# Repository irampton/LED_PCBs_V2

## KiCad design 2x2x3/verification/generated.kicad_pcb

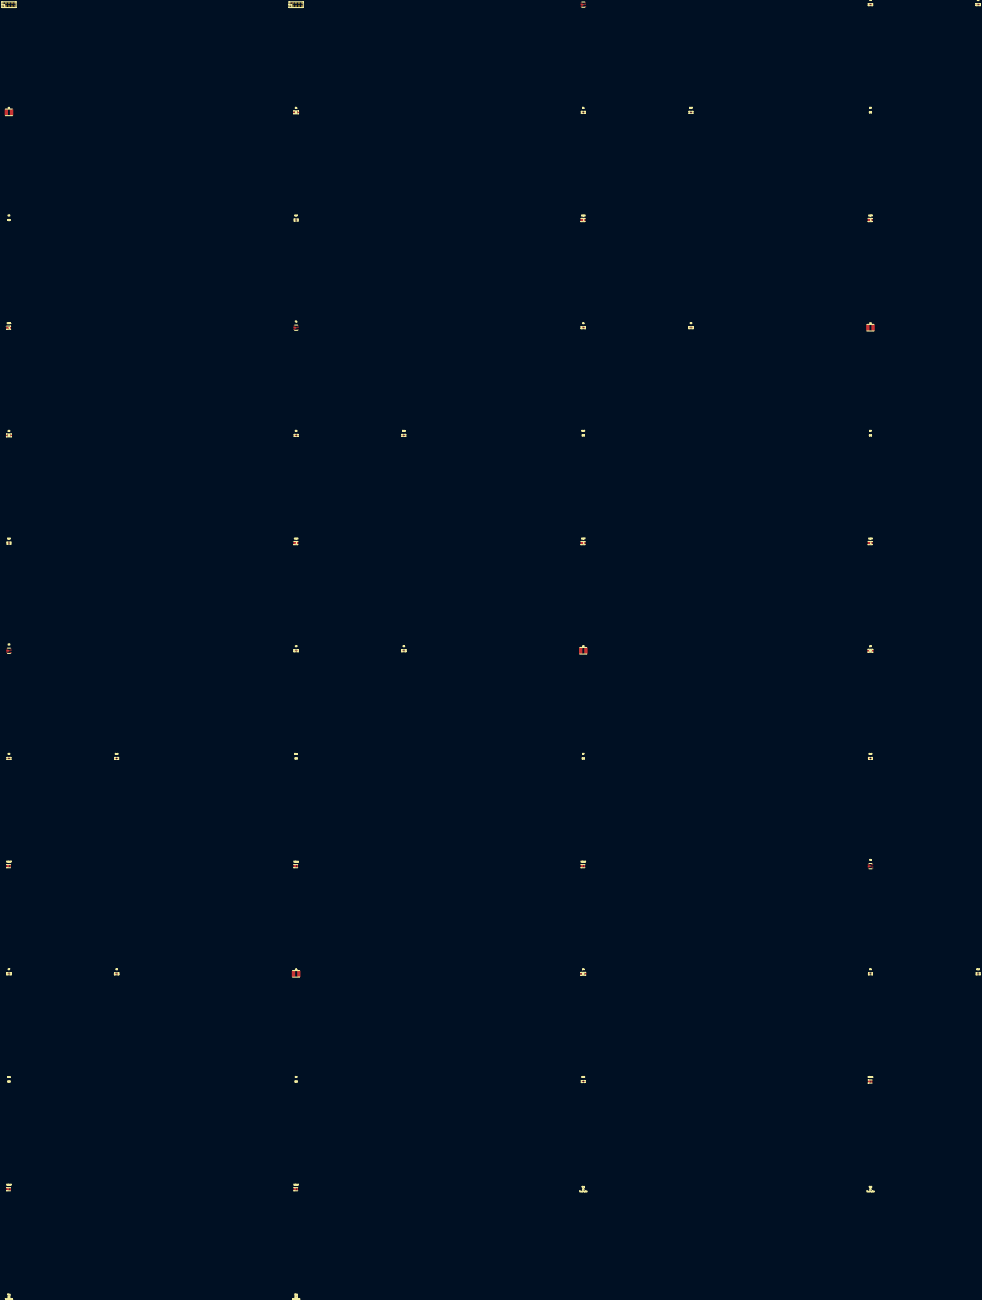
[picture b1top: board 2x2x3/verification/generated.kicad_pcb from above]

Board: 2 copper layers, 58 parts (0 on the bottom side), 28 nets, no tracks yet.

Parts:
C1, C2, C3, C4, C5, C6, C7, C8: 2.2uF; CL21A225KBQNNNE
D1, D2, D3, D4: SS14
H1, H2: PZ2.54-2X5P-H25; PZ2_54_2X5P_H25
L1, L2, L3, L4: 0.000068uH; CY54_68UH
LED2, LED3, LED4, LED6, LED7, LED8: HL-AS-2835D68W-2C-S1-08L-PCT-HR3(R9)-K3(6000K-700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; HL_AS_2835D68W_2C_S1_08L_PCT_HR3_R9_K3_6000K_7000K
LED10, LED11, LED12, LED14, LED15, LED16: HL-AS-2835D68W-2C-S1-08L-PCT-HR3(R9)-K3(2800K-310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; HL_AS_2835D68W_2C_S1_08L_PCT_HR3_R9_K3_2800K_3100K
R1, R2, R3, R4, R13, R14, R15, R16: 1.2; P_0805W8F120KT5E
R5, R6, R7, R8: 100k; P_0402WGF1003TCE
R9, R10, R11, R12: 2.2k; P_0402WGF2201TCE
R17, R18, R19, R20: 10k; P_0805W8F1002T5E
TP1: TestPoint; TestPoint_Pad_1.0x1.0mm
TP2: TestPoint; TestPoint_Pad_1.5x1.5mm
TP3, TP4: TestPoint; TestPoint_Pad_D1.0mm
U1, U2, U3, U4: PT4115

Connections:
GND: C1.2, C2.2, C3.2, C4.2, C5.2, C6.2, C7.2, C8.2, D1.2, D2.2, D3.2, D4.2, H1.2, H1.4, H1.8, H1.10, H2.2, H2.4, H2.8, H2.10, R5.2, R6.2, R7.2, R8.2, TP2.1, U1.2, U2.2, U3.2, U4.2
V+: C1.1, C2.1, C3.1, C4.1, C5.1, C6.1, C7.1, C8.1, H1.1, H1.3, H1.7, H1.9, H2.1, H2.3, H2.7, H2.9, R1.1, R2.1, R3.1, R4.1, R13.1, R14.1, R15.1, R16.1, R17.1, R18.1, R19.1, R20.1, TP1.1, U1.5, U2.5, U3.5, U4.5
cool_a_channel_LED_RETURN: L1.2, LED4.1, R17.2
cool_a_channel_LED_TOP: LED2.2, R1.2, R13.2, U2.4
cool_a_channel_driver_SW: D1.1, L1.1, U2.1
cool_a_channel_pwm_2_2_1: R5.1, R9.2, U2.3
cool_a_leds_1_2: LED2.1, LED3.2
cool_a_leds_2_2: LED3.1, LED4.2
cool_b_channel_LED_RETURN: L2.2, LED8.1, R18.2
cool_b_channel_LED_TOP: LED6.2, R2.2, R14.2, U1.4
cool_b_channel_driver_SW: D2.1, L2.1, U1.1
cool_b_channel_pwm_2_2_1: R6.1, R10.2, U1.3
cool_b_leds_1_2: LED6.1, LED7.2
cool_b_leds_2_2: LED7.1, LED8.2
pwm_cool: H1.5, H2.5, R9.1, R10.1, TP3.1
pwm_warm: H1.6, H2.6, R11.1, R12.1, TP4.1
warm_a_channel_LED_RETURN: L3.2, LED12.1, R19.2
warm_a_channel_LED_TOP: LED10.2, R3.2, R15.2, U3.4
warm_a_channel_driver_SW: D3.1, L3.1, U3.1
warm_a_channel_pwm_2_2_1: R7.1, R11.2, U3.3
warm_a_leds_1_2: LED10.1, LED11.2
warm_a_leds_2_2: LED11.1, LED12.2
warm_b_channel_LED_RETURN: L4.2, LED16.1, R20.2
warm_b_channel_LED_TOP: LED14.2, R4.2, R16.2, U4.4
warm_b_channel_driver_SW: D4.1, L4.1, U4.1
warm_b_channel_pwm_2_2_1: R8.1, R12.2, U4.3
warm_b_leds_1_2: LED14.1, LED15.2
warm_b_leds_2_2: LED15.1, LED16.2

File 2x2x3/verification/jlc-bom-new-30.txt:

JLC BOM estimate for 30 boards

Basic
Designators                 Comment             Footprint         MPN              LCSC #   JLC Stock  Per Board
--------------------------  ------------------  ----------------  ---------------  -------  ---------  ---------
C1, C2, C3, C4, C5, C6,...  2.2uF ±10% 50V X5R  0805              CL21A225KBQNNNE  C377773     965097    $0.2360
D1, D2, D3, D4                                  SMA_L4.2-W2.6...  SS14             C2480      1627295    $0.0768
R5, R6, R7, R8              100kΩ ±1% 62.5mW    0402              0402WGF1003TCE   C25741     8605915    $0.0048
R9, R10, R11, R12           2.2kΩ ±1% 62.5mW    0402              0402WGF2201TCE   C25879     3324376    $0.0044
R17, R18, R19, R20          10kΩ ±1% 125mW      0805              0805W8F1002T5E   C17414    49441463    $0.0136

Extended
Designators                 Comment          Footprint         MPN                         LCSC #     JLC Stock  Per Board
--------------------------  ---------------  ----------------  --------------------------  ---------  ---------  ---------
L1, L2, L3, L4              68uH ±10% 600mA  SMD,5.8x5.2mm     CY54-68UH                   C2929435       12384    $0.1800
LED2, LED3, LED4, LED6,...                   LED-SMD_L3.5-...  HL-AS-2835D68W-2C-S1-08...  C49435731      12953    $0.1800
LED10, LED11, LED12, LE...                   LED-SMD_L3.3-...  HL-AS-2835D68W-2C-S1-08...  C49435727       1153    $0.1830
R1, R2, R3, R4, R13, R1...  1.2Ω ±1% 125mW   0805              0805W8F120KT5E              C17381         26335    $0.0400
U1, U2, U3, U4                               SOT-89-5_L4.5...  PT4115                      C347356        96127    $0.3496

Cost estimate only. These figures ignore board size, layer count, and SMD vs manual assembly.

Economic estimate for 30 boards
  Setup: $8.00
  Stencil: $1.50
  Joints: $2.30
  Extended parts fees: $15.00
  Components: $38.05
  Total estimate: $64.85

Standard estimate for 30 boards
  Setup: $25.00
  Stencil: $7.68
  Joints @ $0.0016: $2.30
  Feed loaders: $15.00
  Components: $38.05
  Total estimate: $88.03

Economic totals
2 boards   $27.59
5 boards   $32.23
15 boards  $45.32
30 boards  $64.85

Standard totals
5 boards     $55.41
30 boards    $88.03
100 boards   $159.62
1000 boards  $960.68

Additional fees may apply: $3.50 hand-soldering, $59.23 large-sized boards, plus x-ray inspection and panel fees.
Double-sided boards require standard assembly, can add $25 setup, and add $7.86 stencil cost.

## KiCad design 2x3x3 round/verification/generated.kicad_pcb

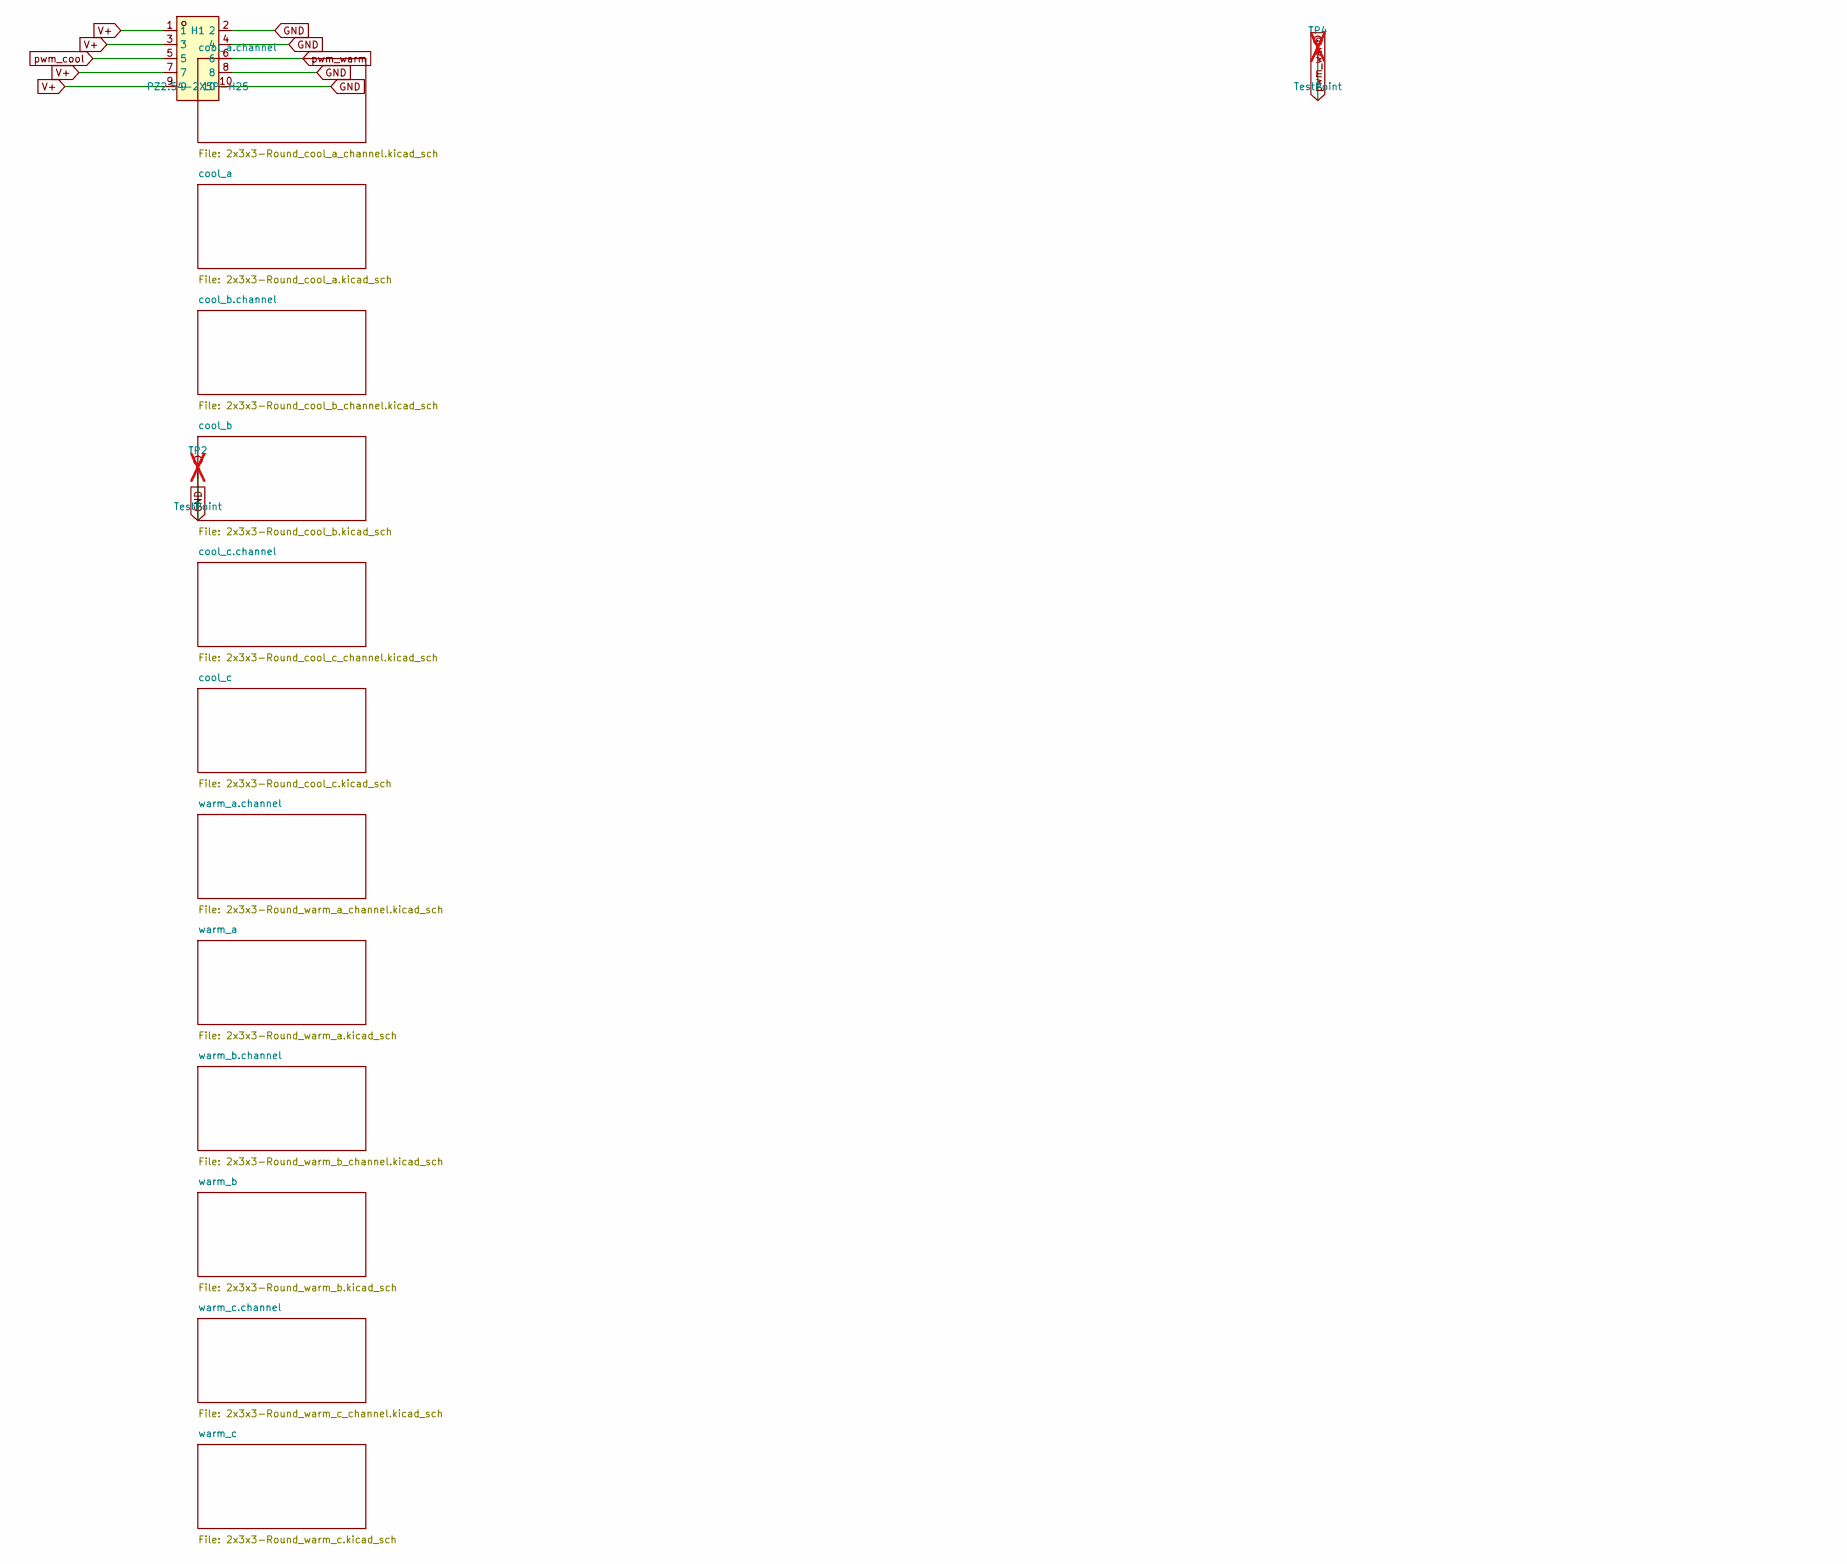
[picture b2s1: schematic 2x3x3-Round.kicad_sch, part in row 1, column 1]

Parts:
H1: PZ2.54-2X5P-H25; PZ2_54_2X5P_H25
TP1: TestPoint; TestPoint_Pad_1.0x1.0mm; not fitted
TP2: TestPoint; TestPoint_Pad_1.5x1.5mm; not fitted
TP3, TP4: TestPoint; TestPoint_Pad_D1.0mm; not fitted

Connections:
GND: H1.2, H1.4, H1.8, H1.10, TP2.1; also elsewhere on the board
V+: H1.1, H1.3, H1.7, H1.9, TP1.1; also elsewhere on the board
pwm_cool: H1.5, TP3.1; also elsewhere on the board
pwm_warm: H1.6, TP4.1; also elsewhere on the board

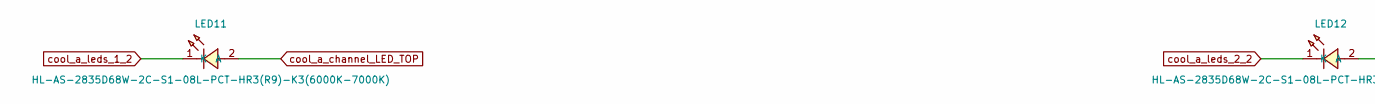
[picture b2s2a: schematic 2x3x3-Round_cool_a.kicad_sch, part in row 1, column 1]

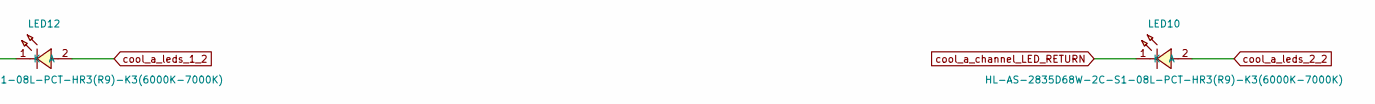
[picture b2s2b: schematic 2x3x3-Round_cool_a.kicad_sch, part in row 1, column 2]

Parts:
LED10, LED11, LED12: HL-AS-2835D68W-2C-S1-08L-PCT-HR3(R9)-K3(6000K-700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; HL_AS_2835D68W_2C_S1_08L_PCT_HR3_R9_K3_6000K_7000K

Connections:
cool_a_channel_LED_RETURN: LED10.1 (K); also elsewhere on the board
cool_a_channel_LED_TOP: LED11.2 (A); also elsewhere on the board
cool_a_leds_1_2: LED11.1 (K), LED12.2 (A)
cool_a_leds_2_2: LED10.2 (A), LED12.1 (K)

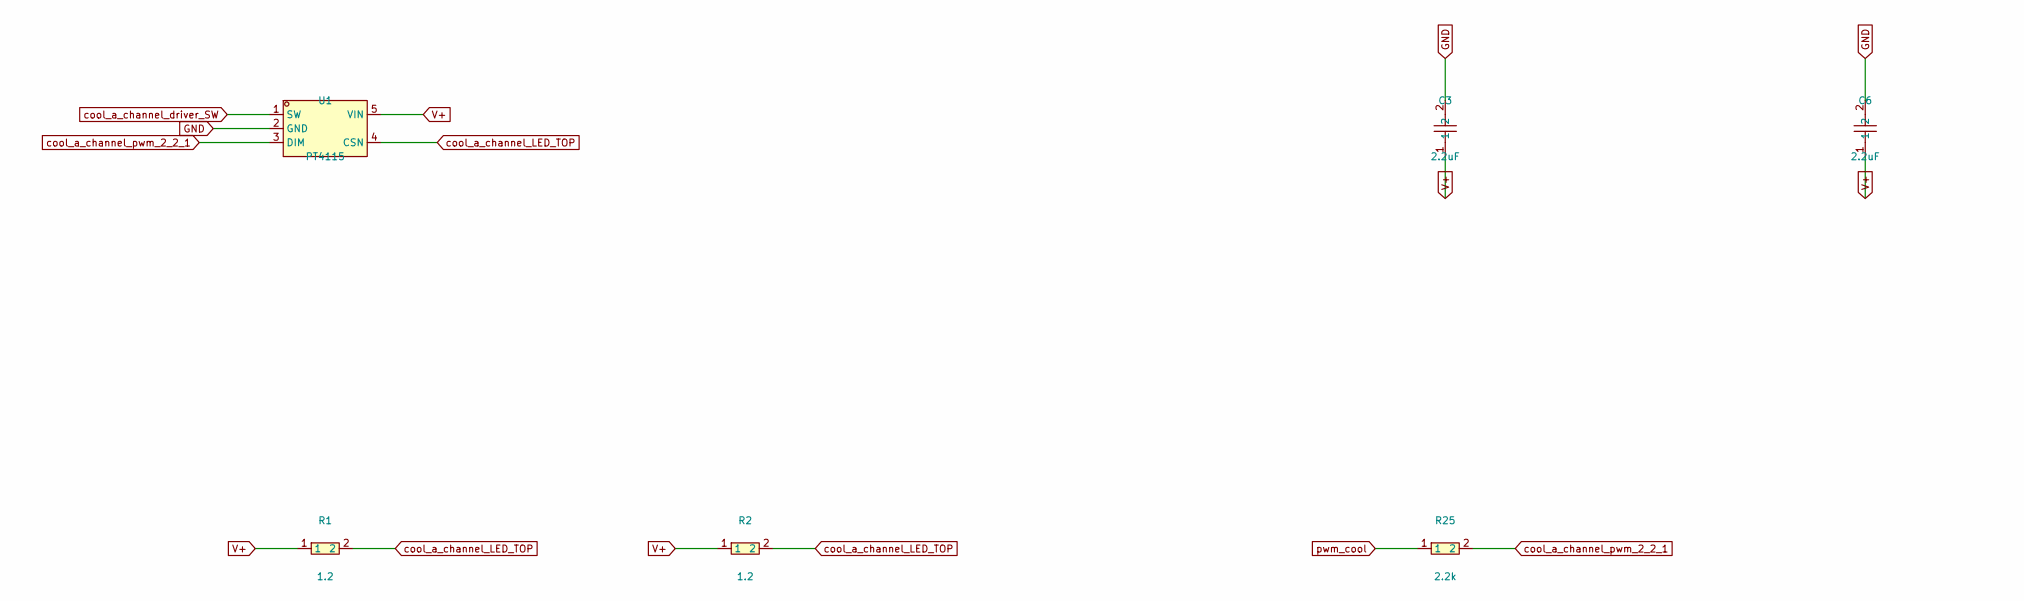
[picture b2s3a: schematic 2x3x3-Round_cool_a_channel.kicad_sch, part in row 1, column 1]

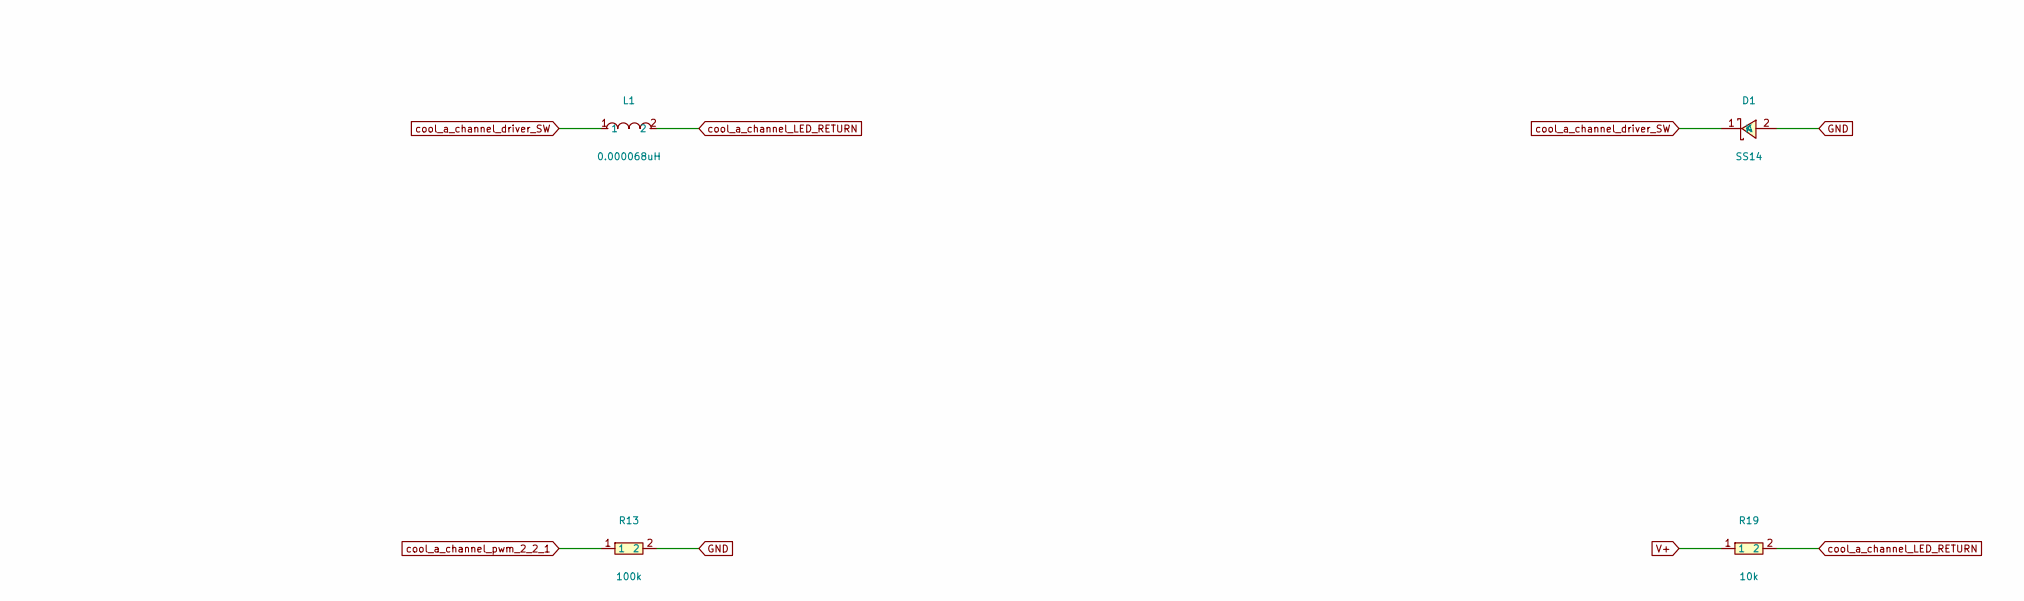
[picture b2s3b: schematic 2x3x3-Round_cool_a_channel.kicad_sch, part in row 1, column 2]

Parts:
C3, C6: 2.2uF; CL21A225KBQNNNE
D1: SS14
L1: 0.000068uH; CY54_68UH
R1, R2: 1.2; P_0805W8F120KT5E
R13: 100k; P_0402WGF1003TCE
R19: 10k; P_0805W8F1002T5E
R25: 2.2k; P_0402WGF2201TCE
U1: PT4115

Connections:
GND: C3.2, C6.2, D1.2 (A), R13.2, U1.2 (GND); also elsewhere on the board
V+: C3.1, C6.1, R1.1, R2.1, R19.1, U1.5 (VIN); also elsewhere on the board
cool_a_channel_LED_RETURN: L1.2, R19.2; also elsewhere on the board
cool_a_channel_LED_TOP: R1.2, R2.2, U1.4 (CSN); also elsewhere on the board
cool_a_channel_driver_SW: D1.1 (K), L1.1, U1.1 (SW)
cool_a_channel_pwm_2_2_1: R13.1, R25.2, U1.3 (DIM)
pwm_cool: R25.1; also elsewhere on the board

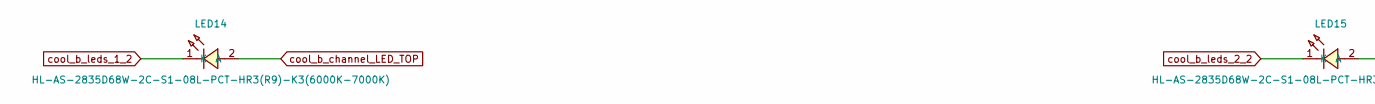
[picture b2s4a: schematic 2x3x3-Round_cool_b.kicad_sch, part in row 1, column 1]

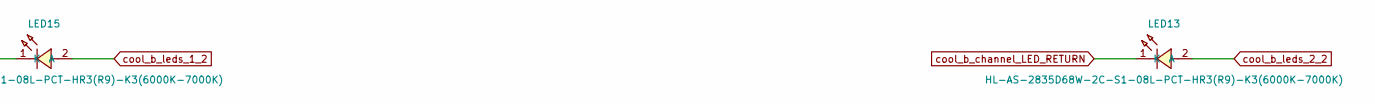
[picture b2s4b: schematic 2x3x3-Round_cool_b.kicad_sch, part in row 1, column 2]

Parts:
LED13, LED14, LED15: HL-AS-2835D68W-2C-S1-08L-PCT-HR3(R9)-K3(6000K-700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; HL_AS_2835D68W_2C_S1_08L_PCT_HR3_R9_K3_6000K_7000K

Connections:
cool_b_channel_LED_RETURN: LED13.1 (K); also elsewhere on the board
cool_b_channel_LED_TOP: LED14.2 (A); also elsewhere on the board
cool_b_leds_1_2: LED14.1 (K), LED15.2 (A)
cool_b_leds_2_2: LED13.2 (A), LED15.1 (K)

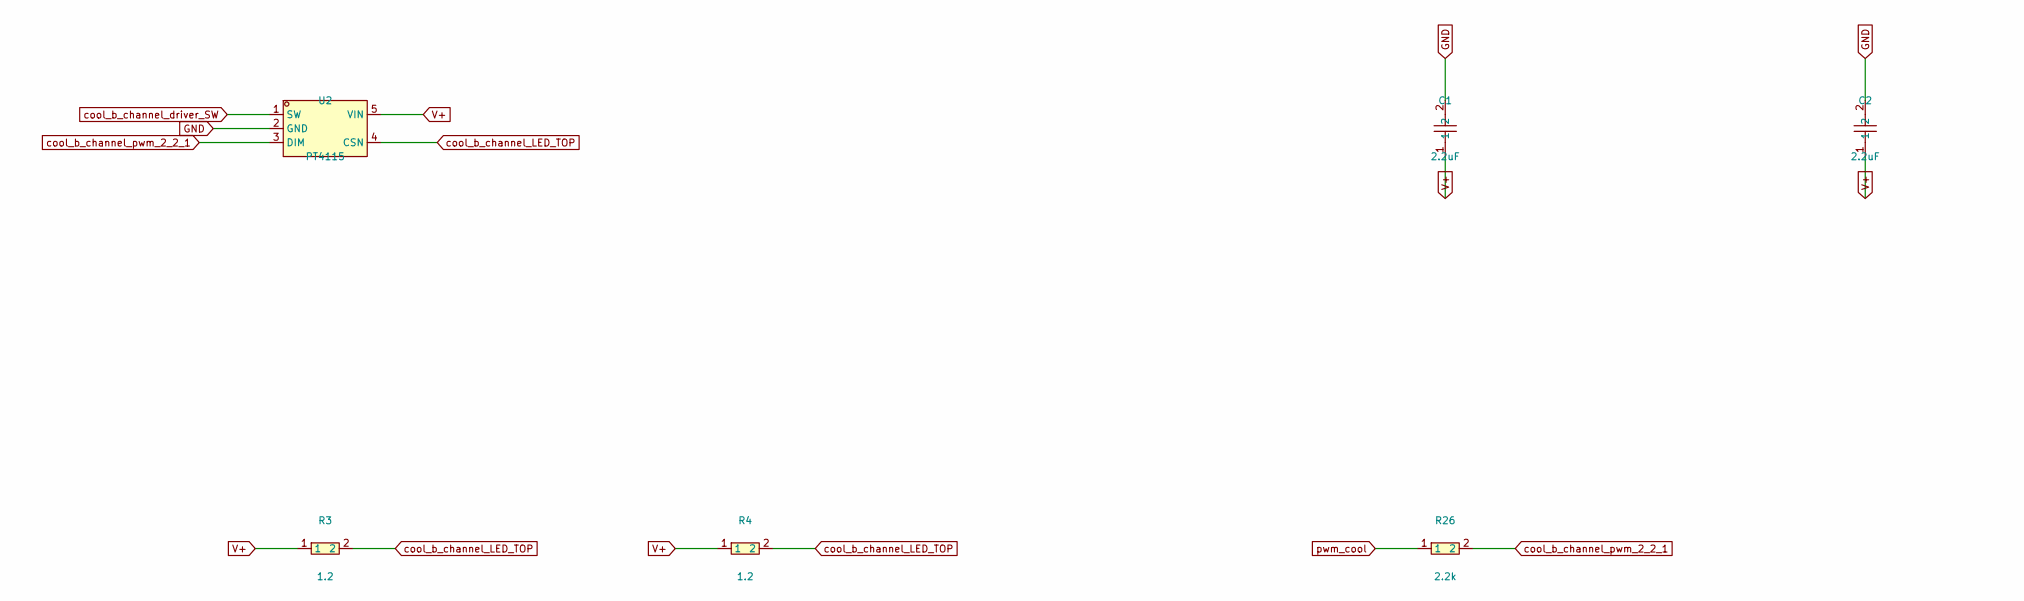
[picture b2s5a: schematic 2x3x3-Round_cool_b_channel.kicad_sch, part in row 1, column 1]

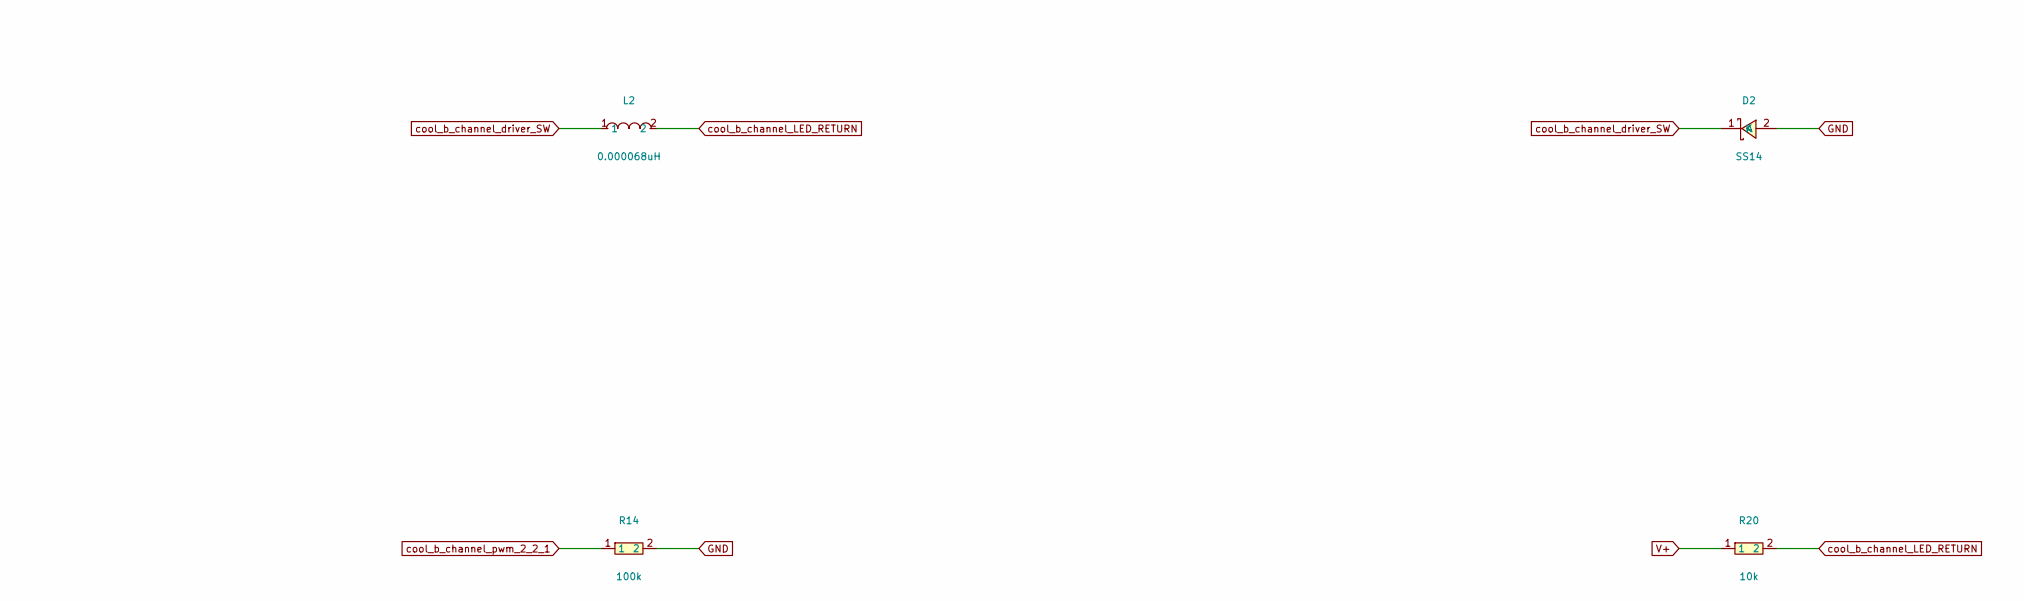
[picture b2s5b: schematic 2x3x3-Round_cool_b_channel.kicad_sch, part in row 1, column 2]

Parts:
C1, C2: 2.2uF; CL21A225KBQNNNE
D2: SS14
L2: 0.000068uH; CY54_68UH
R3, R4: 1.2; P_0805W8F120KT5E
R14: 100k; P_0402WGF1003TCE
R20: 10k; P_0805W8F1002T5E
R26: 2.2k; P_0402WGF2201TCE
U2: PT4115

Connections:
GND: C1.2, C2.2, D2.2 (A), R14.2, U2.2 (GND); also elsewhere on the board
V+: C1.1, C2.1, R3.1, R4.1, R20.1, U2.5 (VIN); also elsewhere on the board
cool_b_channel_LED_RETURN: L2.2, R20.2; also elsewhere on the board
cool_b_channel_LED_TOP: R3.2, R4.2, U2.4 (CSN); also elsewhere on the board
cool_b_channel_driver_SW: D2.1 (K), L2.1, U2.1 (SW)
cool_b_channel_pwm_2_2_1: R14.1, R26.2, U2.3 (DIM)
pwm_cool: R26.1; also elsewhere on the board

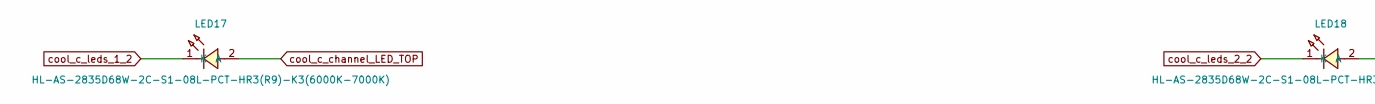
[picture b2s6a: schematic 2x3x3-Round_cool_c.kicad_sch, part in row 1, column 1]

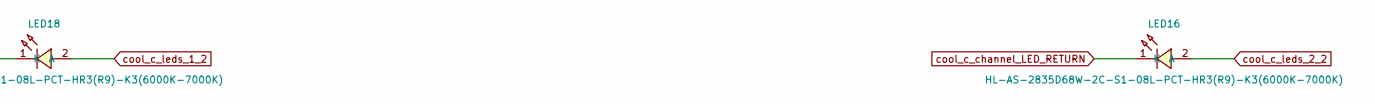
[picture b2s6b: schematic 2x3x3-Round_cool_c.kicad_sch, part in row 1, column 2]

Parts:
LED16, LED17, LED18: HL-AS-2835D68W-2C-S1-08L-PCT-HR3(R9)-K3(6000K-700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; HL_AS_2835D68W_2C_S1_08L_PCT_HR3_R9_K3_6000K_7000K

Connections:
cool_c_channel_LED_RETURN: LED16.1 (K); also elsewhere on the board
cool_c_channel_LED_TOP: LED17.2 (A); also elsewhere on the board
cool_c_leds_1_2: LED17.1 (K), LED18.2 (A)
cool_c_leds_2_2: LED16.2 (A), LED18.1 (K)

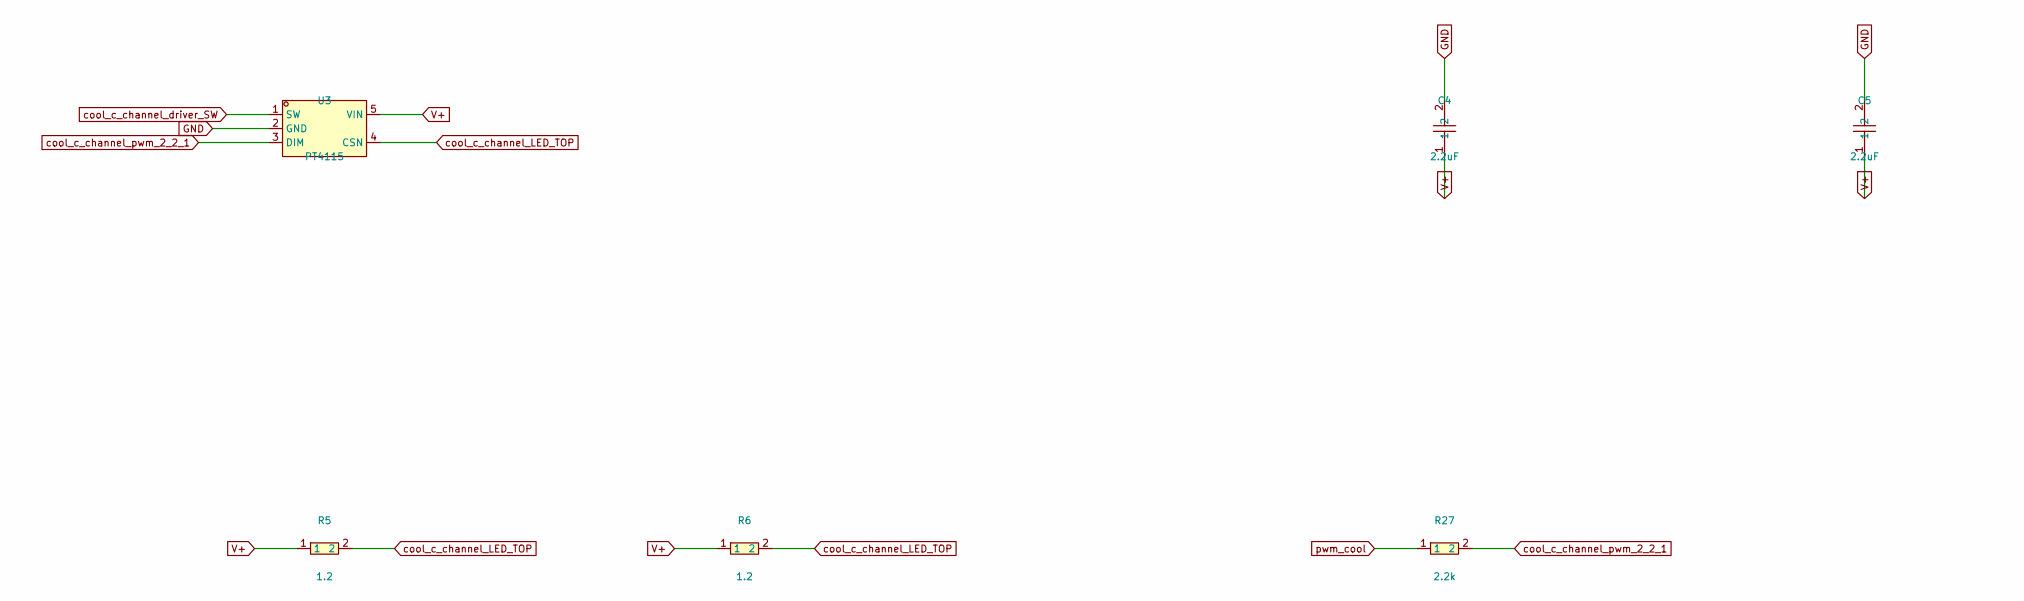
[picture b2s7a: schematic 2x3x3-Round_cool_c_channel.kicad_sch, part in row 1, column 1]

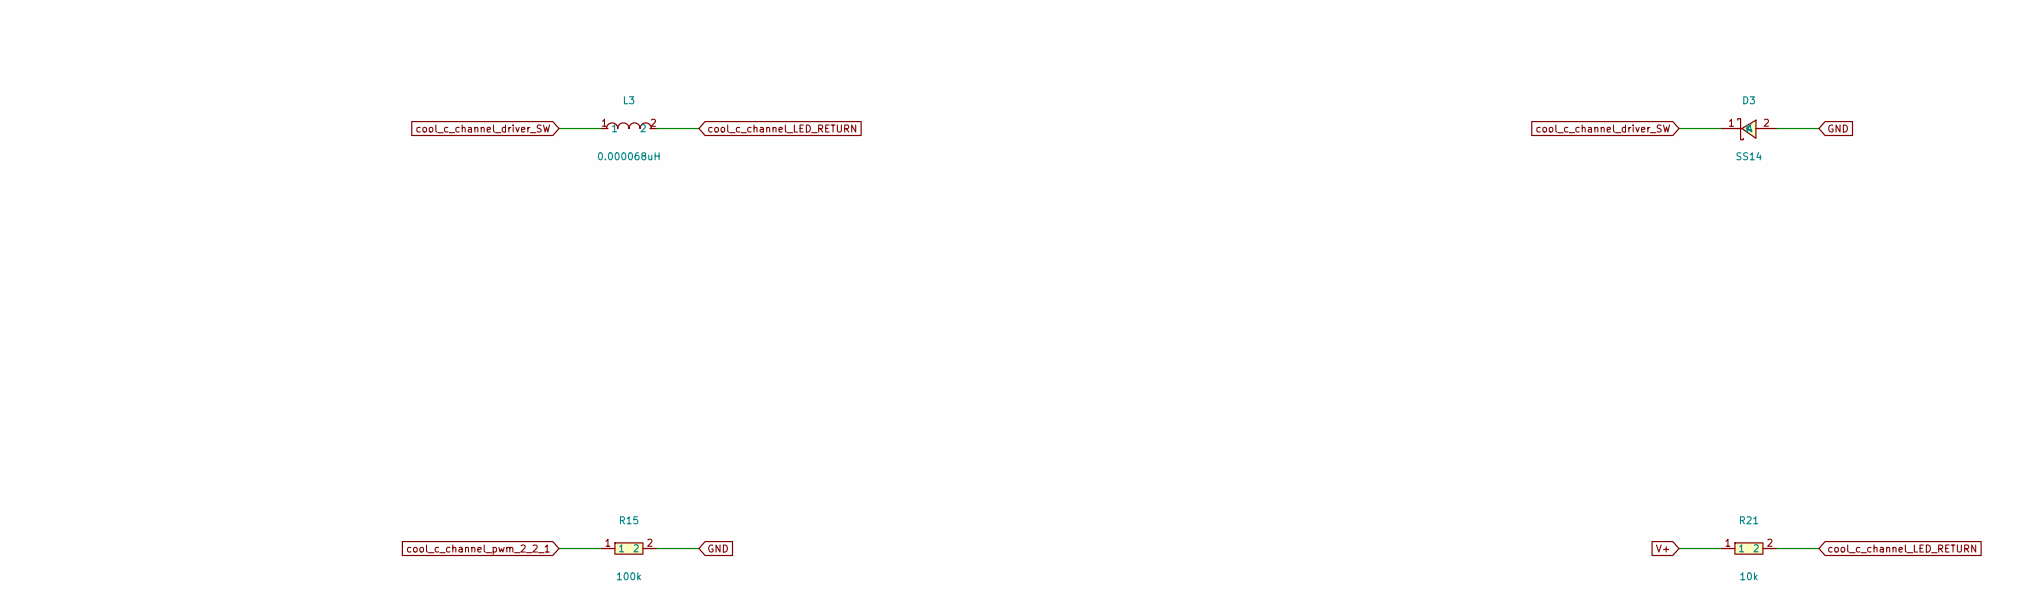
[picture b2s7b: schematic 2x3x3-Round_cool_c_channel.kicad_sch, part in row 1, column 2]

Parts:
C4, C5: 2.2uF; CL21A225KBQNNNE
D3: SS14
L3: 0.000068uH; CY54_68UH
R5, R6: 1.2; P_0805W8F120KT5E
R15: 100k; P_0402WGF1003TCE
R21: 10k; P_0805W8F1002T5E
R27: 2.2k; P_0402WGF2201TCE
U3: PT4115

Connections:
GND: C4.2, C5.2, D3.2 (A), R15.2, U3.2 (GND); also elsewhere on the board
V+: C4.1, C5.1, R5.1, R6.1, R21.1, U3.5 (VIN); also elsewhere on the board
cool_c_channel_LED_RETURN: L3.2, R21.2; also elsewhere on the board
cool_c_channel_LED_TOP: R5.2, R6.2, U3.4 (CSN); also elsewhere on the board
cool_c_channel_driver_SW: D3.1 (K), L3.1, U3.1 (SW)
cool_c_channel_pwm_2_2_1: R15.1, R27.2, U3.3 (DIM)
pwm_cool: R27.1; also elsewhere on the board

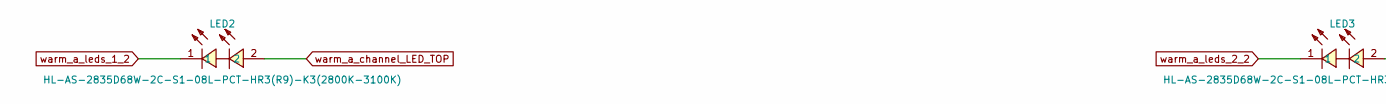
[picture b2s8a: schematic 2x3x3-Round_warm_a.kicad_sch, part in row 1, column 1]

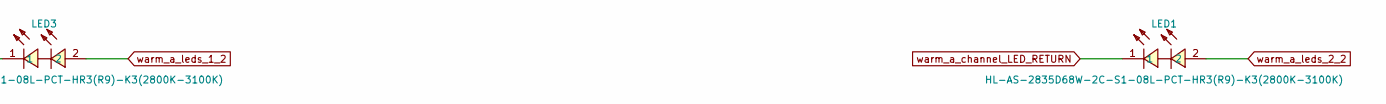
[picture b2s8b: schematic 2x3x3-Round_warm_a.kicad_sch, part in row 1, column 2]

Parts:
LED1, LED2, LED3: HL-AS-2835D68W-2C-S1-08L-PCT-HR3(R9)-K3(2800K-310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; HL_AS_2835D68W_2C_S1_08L_PCT_HR3_R9_K3_2800K_3100K

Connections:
warm_a_channel_LED_RETURN: LED1.1; also elsewhere on the board
warm_a_channel_LED_TOP: LED2.2; also elsewhere on the board
warm_a_leds_1_2: LED2.1, LED3.2
warm_a_leds_2_2: LED1.2, LED3.1

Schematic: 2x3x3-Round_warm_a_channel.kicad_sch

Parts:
C7, C8: 2.2uF; CL21A225KBQNNNE
D4: SS14
L4: 0.000068uH; CY54_68UH
R7, R8: 1.2; P_0805W8F120KT5E
R16: 100k; P_0402WGF1003TCE
R22: 10k; P_0805W8F1002T5E
R28: 2.2k; P_0402WGF2201TCE
U4: PT4115

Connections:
GND: C7.2, C8.2, D4.2 (A), R16.2, U4.2 (GND); also elsewhere on the board
V+: C7.1, C8.1, R7.1, R8.1, R22.1, U4.5 (VIN); also elsewhere on the board
pwm_warm: R28.1; also elsewhere on the board
warm_a_channel_LED_RETURN: L4.2, R22.2; also elsewhere on the board
warm_a_channel_LED_TOP: R7.2, R8.2, U4.4 (CSN); also elsewhere on the board
warm_a_channel_driver_SW: D4.1 (K), L4.1, U4.1 (SW)
warm_a_channel_pwm_2_2_1: R16.1, R28.2, U4.3 (DIM)

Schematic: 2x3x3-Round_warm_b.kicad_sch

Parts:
LED4, LED5, LED6: HL-AS-2835D68W-2C-S1-08L-PCT-HR3(R9)-K3(2800K-310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; HL_AS_2835D68W_2C_S1_08L_PCT_HR3_R9_K3_2800K_3100K

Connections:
warm_b_channel_LED_RETURN: LED4.1; also elsewhere on the board
warm_b_channel_LED_TOP: LED5.2; also elsewhere on the board
warm_b_leds_1_2: LED5.1, LED6.2
warm_b_leds_2_2: LED4.2, LED6.1

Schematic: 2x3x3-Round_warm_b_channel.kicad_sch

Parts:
C9, C10: 2.2uF; CL21A225KBQNNNE
D5: SS14
L5: 0.000068uH; CY54_68UH
R9, R10: 1.2; P_0805W8F120KT5E
R17: 100k; P_0402WGF1003TCE
R23: 10k; P_0805W8F1002T5E
R29: 2.2k; P_0402WGF2201TCE
U5: PT4115

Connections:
GND: C9.2, C10.2, D5.2 (A), R17.2, U5.2 (GND); also elsewhere on the board
V+: C9.1, C10.1, R9.1, R10.1, R23.1, U5.5 (VIN); also elsewhere on the board
pwm_warm: R29.1; also elsewhere on the board
warm_b_channel_LED_RETURN: L5.2, R23.2; also elsewhere on the board
warm_b_channel_LED_TOP: R9.2, R10.2, U5.4 (CSN); also elsewhere on the board
warm_b_channel_driver_SW: D5.1 (K), L5.1, U5.1 (SW)
warm_b_channel_pwm_2_2_1: R17.1, R29.2, U5.3 (DIM)

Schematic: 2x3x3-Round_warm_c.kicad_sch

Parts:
LED7, LED8, LED9: HL-AS-2835D68W-2C-S1-08L-PCT-HR3(R9)-K3(2800K-310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; HL_AS_2835D68W_2C_S1_08L_PCT_HR3_R9_K3_2800K_3100K

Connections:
warm_c_channel_LED_RETURN: LED7.1; also elsewhere on the board
warm_c_channel_LED_TOP: LED8.2; also elsewhere on the board
warm_c_leds_1_2: LED8.1, LED9.2
warm_c_leds_2_2: LED7.2, LED9.1
